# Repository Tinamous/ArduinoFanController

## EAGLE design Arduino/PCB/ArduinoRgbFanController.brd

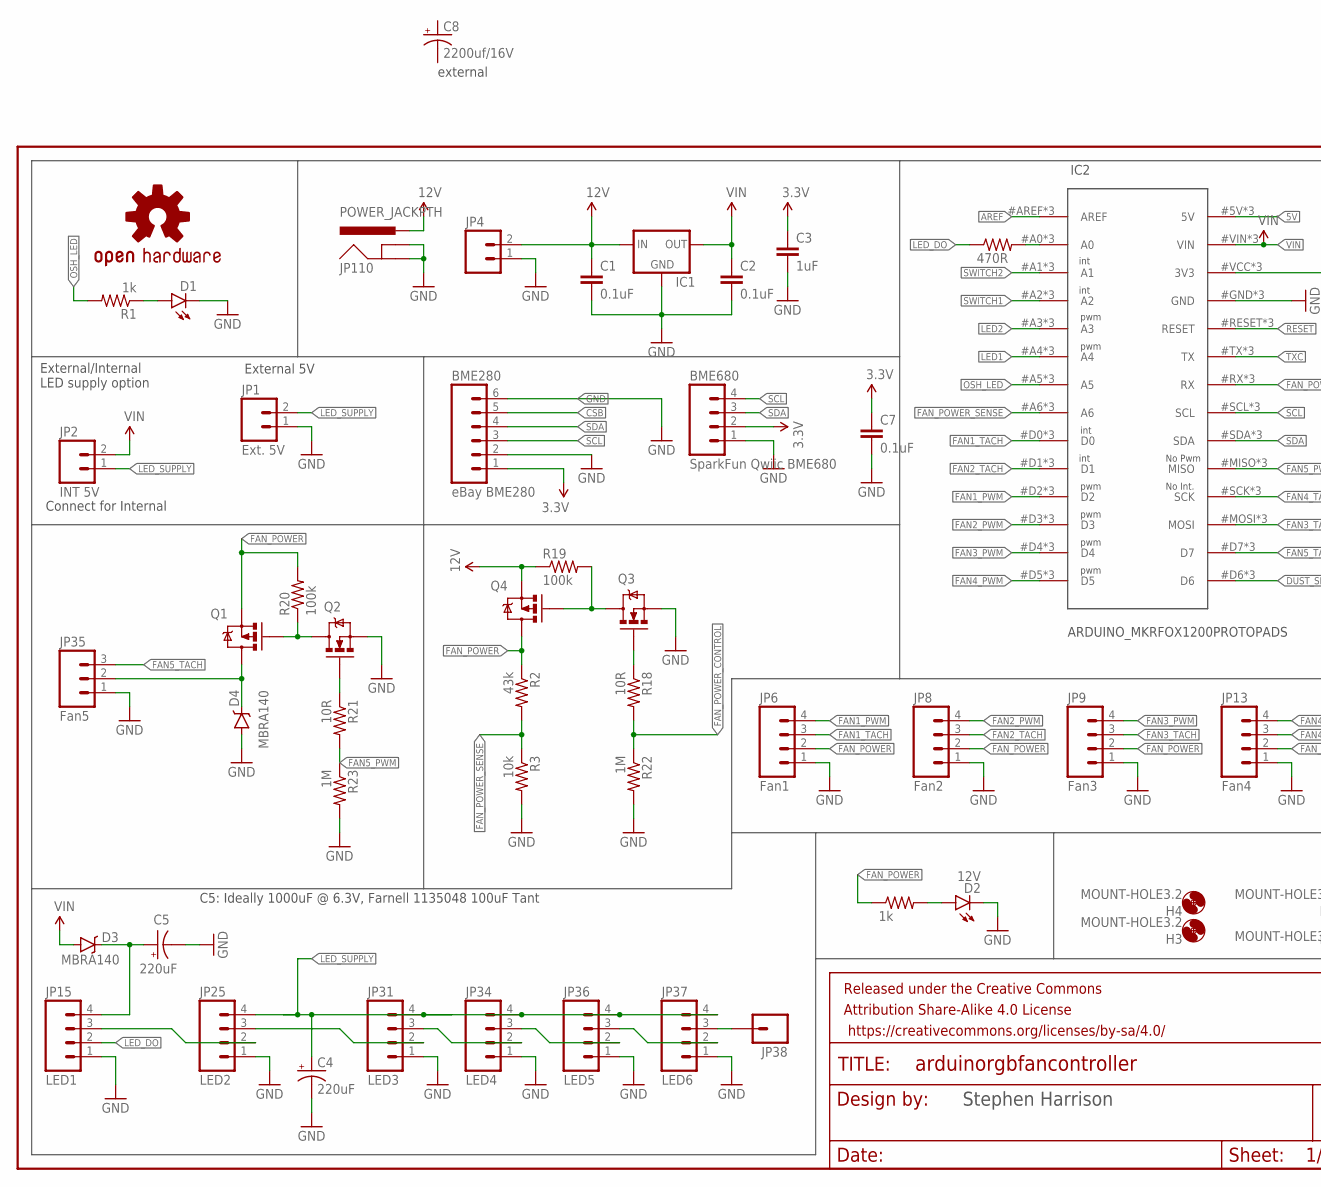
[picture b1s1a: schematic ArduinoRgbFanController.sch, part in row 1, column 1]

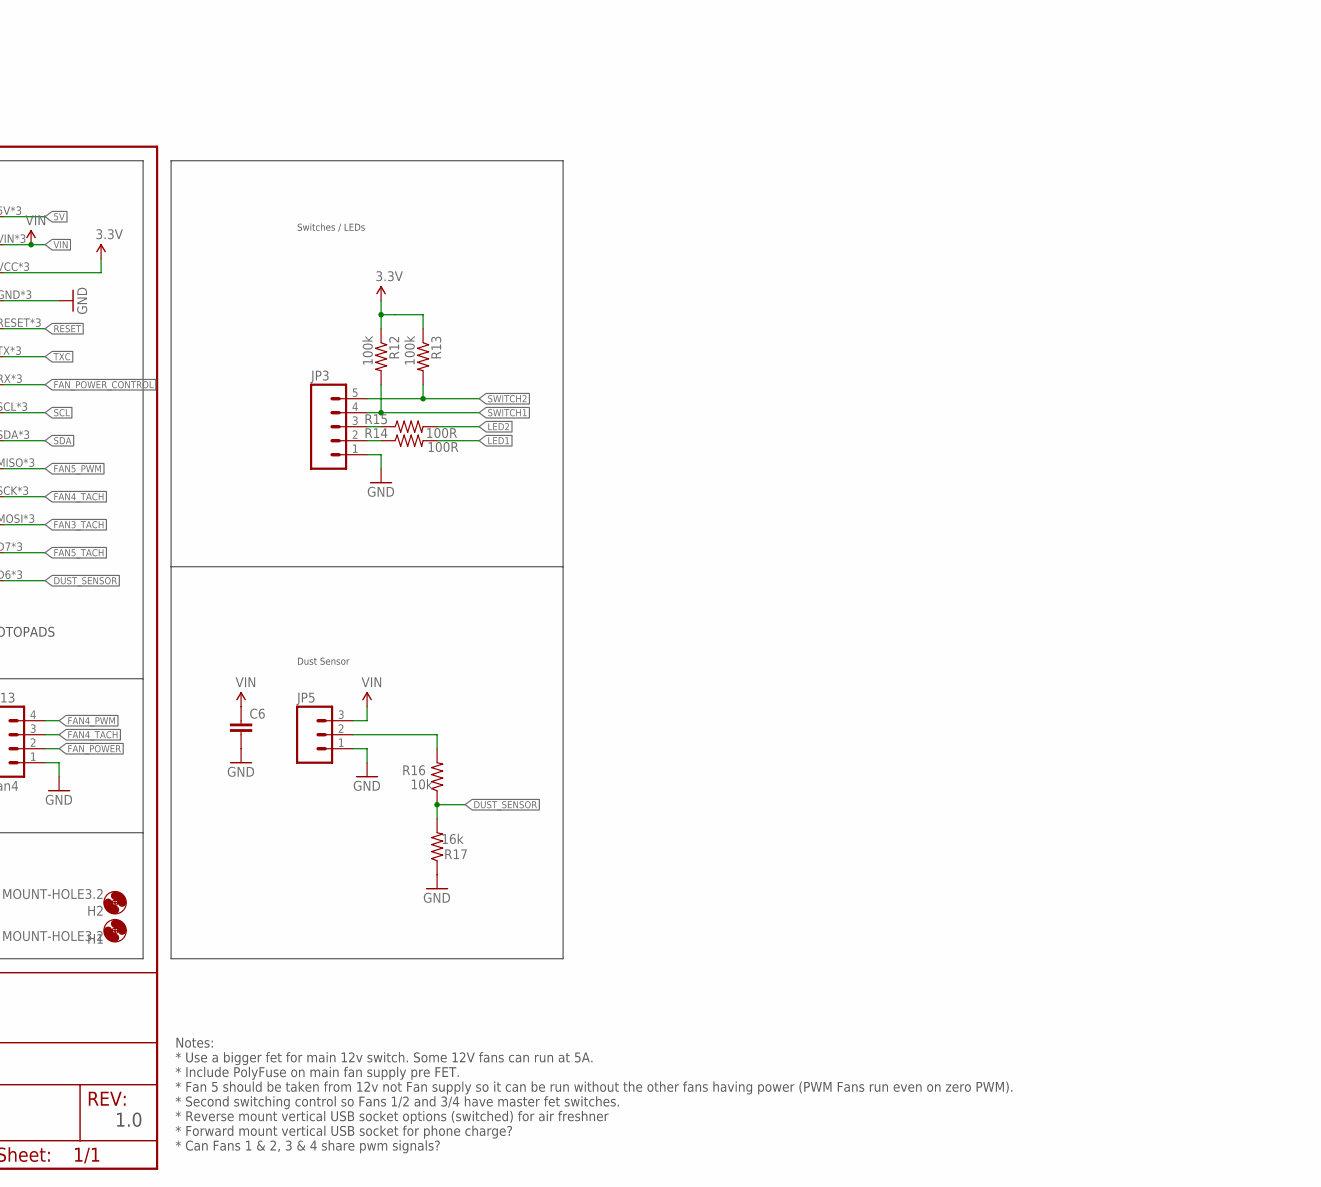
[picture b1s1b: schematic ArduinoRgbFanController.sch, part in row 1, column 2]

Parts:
BME280: eBay BME280; 1X06
BME680: SparkFun Qwiic BME680; 1X04
C1, C2, C7: 0.1uF; 0805-CAP
C3: 1uF; 0805-CAP
C4, C5: 220uF; EIA3528; FARNELL 2491486
C6: 1UF-25V-10%(0805)"; 0805-CAP
C8: 2200uf/16V; CPOL-RADIAL-1000UF-25V-KIT
D1: LED1206-BOTTOM; LED-1206-BOTTOM
D2: 12V; LED-1206
D3, D4: MBRA140; SMA-DIODE
FRAME1: FRAME-LETTER; CREATIVE_COMMONS
H1, H2, H3, H4: MOUNT-HOLE3.2; 3,2
IC1: 78XXS
IC2: ARDUINO_MKRFOX1200PROTOPADS; ARDUINO_MKRFOX1200_PROTOPADS
JP1: Ext. 5V; SCREWTERMINAL-3.5MM-2
JP2: INT 5V; 1X02
JP3: M05PTH; 1X05
JP4: M025MM; SCREWTERMINAL-5MM-2
JP5: M03POLAR; MOLEX-1X3
JP6: Fan1; MOLEX-1X4; FARNELL 2313705
JP8: Fan2; MOLEX-1X4
JP9: Fan3; MOLEX-1X4
JP13: Fan4; MOLEX-1X4
JP15: LED1; 1X04; FARNELL 2063775
JP25: LED2; 1X04; FARNELL 2063775
JP31: LED3; 1X04; FARNELL 2063775
JP34: LED4; 1X04; FARNELL 2063775
JP35: Fan5; MOLEX-1X3
JP36: LED5; 1X04; FARNELL 2063775
JP37: LED6; 1X04; FARNELL 2063775
JP38: M01PTH; 1X01
JP110: POWER_JACKPTH; POWER_JACK_PTH
LOGO3: OSHW-LOGOM; OSHW-LOGO-M
Q1, Q4: IRLML930; SOT23-3; FARNELL 1831089
Q2, Q3: 2N7002; SOT23-3; FARNELL 1510761
R1: 1k; 0805
R2: 43k; 0805
R3, R16: 10k; 0805
R11: 470R; 0805
R12, R13, R19, R20: 100k; 0805
R14, R15: 100R; 0805
R17: 16k; 0805
R18, R21: 10R; 0805
R22, R23: 1M; 0805
R28: 1k; 1206

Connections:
3.3V: BME280.1, BME680.2, C3.1, C7.1, IC2.#VCC (3V3), IC2.@VCC (3V3), IC2.VCC (3V3), R12.1, R13.1
5V: IC2.5V, IC2.#5V (5V), IC2.@5V (5V)
12V: C1.1, IC1.IN, JP4.2, JP110.PWR, Q4.2 (S), R19.1
AREF: IC2.#AREF (AREF), IC2.@AREF (AREF), IC2.AREF
CSB: BME280.5
DUST_SENSOR: IC2.#D6 (D6), IC2.@D6 (D6), IC2.D6, R16.1, R17.2
FAN1_PWM: IC2.#D2 (D2), IC2.@D2 (D2), IC2.D2, JP6.4
FAN1_TACH: IC2.#D0 (D0), IC2.@D0 (D0), IC2.D0, JP6.3
FAN2_PWM: IC2.#D3 (D3), IC2.@D3 (D3), IC2.D3, JP8.4
FAN2_TACH: IC2.#D1 (D1), IC2.@D1 (D1), IC2.D1, JP8.3
FAN3_PWM: IC2.#D4 (D4), IC2.@D4 (D4), IC2.D4, JP9.4
FAN3_TACH: IC2.#MOSI (MOSI), IC2.@MOSI (MOSI), IC2.MOSI, JP9.3
FAN4_PWM: IC2.#D5 (D5), IC2.@D5 (D5), IC2.D5, JP13.4
FAN4_TACH: IC2.#SCK (SCK), IC2.@SCK (SCK), IC2.SCK, JP13.3
FAN5_PWM: IC2.#MISO (MISO), IC2.@MISO (MISO), IC2.MISO, R21.2, R23.1
FAN5_TACH: IC2.#D7 (D7), IC2.@D7 (D7), IC2.D7, JP35.3
FAN_POWER: JP6.2, JP8.2, JP9.2, JP13.2, Q1.2 (S), Q4.3 (D), R2.1, R20.2, R28.1
FAN_POWER_CONTROL: IC2.#RX (RX), IC2.@RX (RX), IC2.RX, R18.2, R22.1
FAN_POWER_SENSE: IC2.#A6 (A6), IC2.@A6 (A6), IC2.A6, R2.2, R3.1
GND: BME280.2, BME280.6, BME680.1, C1.2, C2.2, C3.2, C4.C (-), C5.C (-), C6.2, C7.2, D1.C, D2.C, D4.A, IC1.GND, IC2.#GND (GND), IC2.@GND (GND), IC2.GND, JP1.1, JP3.1, JP4.1, JP5.1, JP6.1, JP8.1, JP9.1, JP13.1, JP15.1, JP25.1, JP31.1, JP34.1, JP35.1, JP36.1, JP37.1, JP110.GND, JP110.GNDBREAK, Q2.2 (S), Q3.2 (S), R3.2, R17.1, R22.2, R23.2
LED1: IC2.#A4 (A4), IC2.@A4 (A4), IC2.A4, R14.2
LED2: IC2.#A3 (A3), IC2.@A3 (A3), IC2.A3, R15.2
LED_DO: JP15.2, R11.1
LED_SUPPLY: C4.A (+), JP1.2, JP2.1, JP25.4, JP31.4, JP34.4, JP36.4, JP37.4
unnamed: D1.A, R1.1
unnamed: IC2.#A0 (A0), IC2.@A0 (A0), IC2.A0, R11.2
unnamed: JP3.2, R14.1
unnamed: JP3.3, R15.1
unnamed: Q3.3 (D), Q4.1 (G), R19.2
unnamed: Q3.1 (G), R18.1
unnamed: JP5.2, R16.2
unnamed: D4.C, JP35.2, Q1.3 (D)
unnamed: C5.A (+), D3.C, JP15.4
unnamed: JP25.3, JP31.2
unnamed: JP31.3, JP34.2
unnamed: JP34.3, JP36.2
unnamed: JP36.3, JP37.2
unnamed: JP37.3, JP38.1
unnamed: Q1.1 (G), Q2.3 (D), R20.1
unnamed: JP15.3, JP25.2
unnamed: Q2.1 (G), R21.1
unnamed: D2.A, R28.2
OSH_LED: IC2.#A5 (A5), IC2.@A5 (A5), IC2.A5, R1.2
RESET: IC2.#RESET (RESET), IC2.@RESET (RESET), IC2.RESET
SCL: BME280.3, BME680.4, IC2.#SCL (SCL), IC2.@SCL (SCL), IC2.SCL
SDA: BME280.4, BME680.3, IC2.#SDA (SDA), IC2.@SDA (SDA), IC2.SDA
SWITCH1: IC2.#A2 (A2), IC2.@A2 (A2), IC2.A2, JP3.4, R12.2
SWITCH2: IC2.#A1 (A1), IC2.@A1 (A1), IC2.A1, JP3.5, R13.2
TXC: IC2.#TX (TX), IC2.@TX (TX), IC2.TX
VIN: C2.1, C6.1, D3.A, IC1.OUT, IC2.#VIN (VIN), IC2.@VIN (VIN), IC2.VIN, JP2.2, JP5.3

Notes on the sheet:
1.0
Stephen Harrison
External/Internal LED supply option
External 5V
Connect for Internal
Switches / LEDs
Dust Sensor
No Int.
No Pwm
int
pwm
Notes: * Use a bigger fet for main 12v switch. Some 12V fans can run at 5A. * Include PolyFuse on main fan supply pre FET. * Fan 5 should be taken from 12v not Fan supply so it can be run without the other fans having power (PWM Fans run even on zero PWM). * Second switching control so Fans 1/2 and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
C5: Ideally 1000uF @ 6.3V, Farnell 1135048 100uF Tant
external

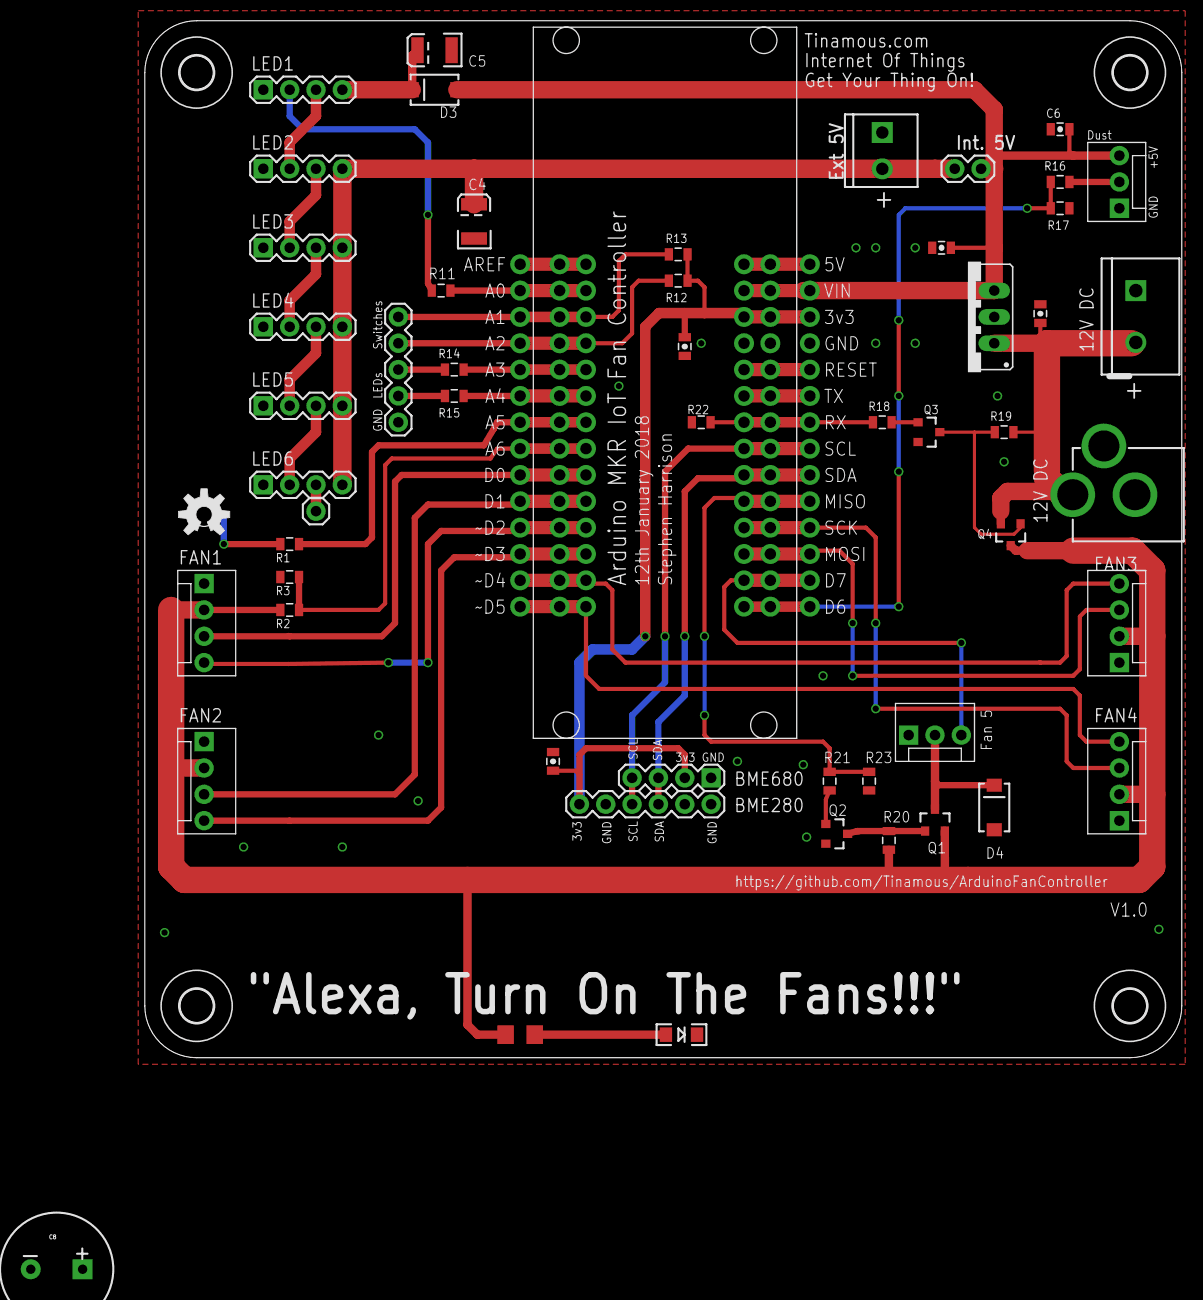
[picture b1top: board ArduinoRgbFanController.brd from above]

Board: 2 copper layers, 100.0 x 100.0 mm, 61 parts (1 on the bottom side), 49 nets.

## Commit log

2018-01-13 Initial version, as sent to DirtyPCBs
2018-01-13 Tidied up schematic.
    Added values to resistors.
2018-01-14 Updated to add dust sensor and switch/led drivers. Updated files at DirtyPCBs
2018-01-14 Moved dust sensor connection to PCB edge.
    Removed pullup/down resistors for PWM and tach signals as they are not needed.
    Added P-FET + N-FET power control to switch the 12V to the PWM fans as some fans do not switch off when PWM off.
    Moved 12V LED to switched fan power line and to underneath the "On" lettering.
2018-01-14 Updated schematic image.
2018-01-14 Added 12v sense to detect low voltage and supply switched on.
    Moved Fan5 connector up to leave a nice space at the bottom for the "Alexa..." thing.
2018-01-15 First pass case parts for a really useful box based filter box.
2018-01-15 Adjusted filter for narrower cutouts as on 120mm fan these clash.
2018-01-15 Enclosure for electronics
2018-01-15 Spacer to allow for an up-side-down lid to be placed on top of the fan lid.
2018-01-15 Added electronics enclosure to the build script.
2018-01-15 Rebuild stl's
2018-01-15 Start of acrylic case for fans
2018-01-15 Tidied up
2018-01-15 Added adaptor plate for 120mm fan to fit in 140mm hole.
2018-01-16 Added build options for filterframe for 3x3 and 6x6 grid.
2018-01-17 Corrected fan filter build, added neopixel switch and holder, commented out 120mm fans for a bit as not using those parts at this time.
2018-01-17 Increased post heigth by pcb 1mm (and referenced base of box). Made box 2mm deeper to allow for this.
    Added hole for 40mm fan to draw air in when not running main fans.
    added mount for a CCS811 Sparkfun breakout board on the back of the box (inside the really dusty box).
2018-01-17 Added svg (and generated png/pdf) for box top cutout for 140 and 120mm fans.
2018-01-17 Changed to use +ve z rather than -ve to save confusion.
    Fixed height, was supposed to be 60mm open top, but with -ve z and base placement (+ve z) it was more.
2018-01-17 Updated sized.
2018-01-17 Increased the base plate size of the 140mm fan adaptor so that it more than covers the 140mm hole.
    Added countersinks for 120mm fan so that the plate can fit flush.
2018-01-17 Changed how the frame is build to put rectangles across rather than cut holes in hope of making printing better (didn't).
    Adde svg generator for drilling guide (doesn't appear to line up).
    Otherwise a successful update....
2018-01-17 Made the spacer slightly larger with a bigger hole.
2018-01-17 Plate to hold 24 pixel neopixel ring and switch when not using fan LEDs and otherwise mounted button.
2018-01-17 Drilling guide for the side walls of the case.
2018-01-17 Rebuild (unchanged)
2018-01-17 Work in progress for cutting template for 4 fan unit.
2018-01-17 Start of Arduino application.
2018-01-21 Fan led exercisor to set fan colours acording to sensor values
2018-01-21 Tidied up a little and fixed bug with fan nose not using the factored temperature.
2018-01-21 Added humidity display
2018-01-21 Changed fan led display so that full range is 12, 1, 2... 11 and 12, 11, 10..1
    Added start of Air Quality range.
2018-01-23 Test/Development code for getting the fans, LEDs and MQTT link running.
2018-01-23 Added some value for components and some notes and dimensions for the PCB.
2018-01-23 First pass at the laser cutting template for the fans box.
2018-01-23 Moved 3D printing bits to own folders so build can do individual ones.
2018-01-23 Added gitignore
2018-01-27 Added fancy mode for LED driving.
2018-01-27 Test program for the Arduino to connect to Tinamous MQTT server.
2018-01-27 Main box of four fans application to run the fans and LEDs as well as connect to the Tinamous MQTT service
2018-01-27 svg's and dxfs for box laser cutting.
2018-01-27 Various 3D printing spacers for
2018-01-28 Added in MQTT connectivity.
    Moved a few more fan settings to the fan struct.
    Added a few more display types.
2018-01-28 Split out the cover plates to individual ones and added WiFi signal.t
2018-01-28 Updated fan guard spacer so it's now cone shaped with M4 at one end to connect onto fan bolt and M3 at the other for a screw in from the cover plate.
2018-01-28 Improved MQTT interactions.
2018-01-29 Added status messaging and tidied up a little.
2018-02-13 Updated fan guard spacer to take M4 heat fit insert fan side, and M3 guard side in a cone shape to reduce visability.
2018-02-13 Start of fan outlet components.
2018-02-13 Modified dusty box filter frame for inside/outside. 8mm/18mm thickness versions for carbon and dust filters either inside or outside.
    Split original scad file into inside/outside and retainer - not using retainer currently.
2018-02-13 Updated component values whilst building boards.
2018-02-13 Added sensors file to read/update sensor values.
    Removed fan4 (pin 9) interrupt as this isn't working and it may not support interrupts....
    Updated MQTT to include measured fan voltage and added some more response commands.
2018-02-13 Started readme
2018-02-20 Added various outlets and blanking plates.
2018-02-20 Added required external capacitor and part values.
2018-02-20 Tidied up, added support for switches and switch LEDs.
    Changed speeed and led brightness to be % to work better with Alexa.
    Added support for light sensor.
    Improved boot sequence.
    Added a delay to loop based on fan speed so fan speed animations (i.e. strip pixels) are representative of the fan speed.
    Added support for BME680 and light sensor.
    Added support for LED strips of 120/M for around the fans at the front and vertical facing at the back.

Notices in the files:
parts and their libraries:
SparkFun-Capacitors: Licensing: Creative Commons ShareAlike 4.0 International - https://creativecommons.org/licenses/by-sa/4.0
SparkFun-Aesthetics: Released under the Creative Commons Attribution Share-Alike 4.0 License
SparkFun-Aesthetics: https://creativecommons.org/licenses/by-sa/4.0
